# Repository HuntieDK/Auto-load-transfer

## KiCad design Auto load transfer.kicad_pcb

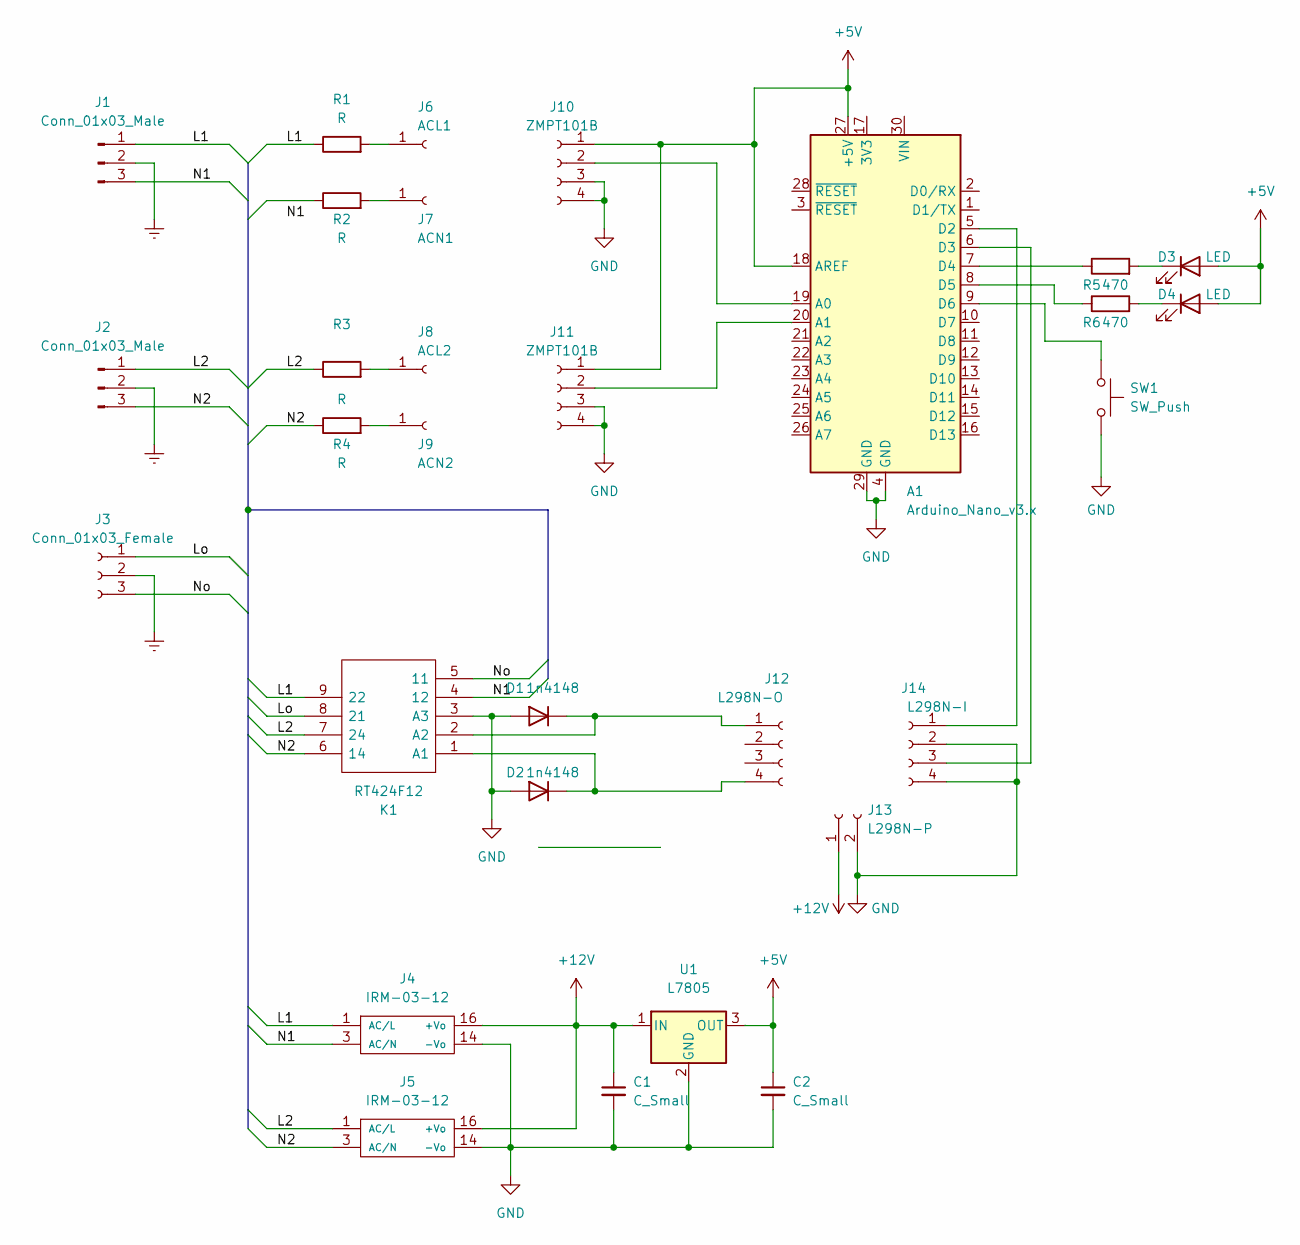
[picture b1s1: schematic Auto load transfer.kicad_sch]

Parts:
A1: Arduino_Nano_v3.x; Arduino_Nano
C1, C2: C_Small; C_Disc_D5.0mm_W2.5mm_P5.00mm
D1, D2: 1n4148; D_DO-35_SOD27_P7.62mm_Horizontal
D3, D4: LED; TerminalBlock_bornier-2_P5.08mm
J1, J2: Conn_01x03_Male; TerminalBlock_bornier-3_P5.08mm
J3: Conn_01x03_Female; TerminalBlock_bornier-3_P5.08mm
J4, J5: IRM-03-12; MeanWell_IRM
J6: ACL1; MountingHole_2.2mm_M2_DIN965_Pad
J7: ACN1; MountingHole_2.2mm_M2_DIN965_Pad
J8: ACL2; MountingHole_2.2mm_M2_DIN965_Pad
J9: ACN2; MountingHole_2.2mm_M2_DIN965_Pad
J10, J11: ZMPT101B; PinHeader_1x04_P2.54mm_Vertical
J12: L298N-O; PinHeader_1x04_P2.54mm_Vertical
J13: L298N-P; PinHeader_1x02_P2.54mm_Vertical
J14: L298N-I; PinHeader_1x04_P2.54mm_Vertical
K1: RT424F12; Manufacturer_Part_Number RT424F12; Mouser Part Number 655-RT424F12
R1, R2, R3, R4: R; R_Axial_DIN0309_L9.0mm_D3.2mm_P12.70mm_Horizontal
R5, R6: 470; R_Axial_DIN0309_L9.0mm_D3.2mm_P12.70mm_Horizontal
SW1: SW_Push; TerminalBlock_bornier-2_P5.08mm
U1: L7805; TO-220-3_Vertical

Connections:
+5V: A1.18 (AREF), A1.27 (+5V), C2.1, D3.2 (A), D4.2 (A), J10.1, J11.1, U1.3 (OUT)
+12V: C1.1, J4.16 (+Vo), J5.16 (+Vo), J13.1, U1.1 (IN)
/L1: J1.1, J4.1 (AC/L), K1.9 (22), R1.1
/L2: J2.1, J5.1 (AC/L), K1.7 (24), R3.1
/Lo: J3.1, K1.8 (21)
/N1: J1.3, J4.3 (AC/N), K1.4 (12)
/N2: J2.3, J5.3 (AC/N), K1.6 (14), R4.1
/No: J3.3, K1.5 (11)
Earth: J1.2, J2.2, J3.2
GND: A1.4 (GND), A1.29 (GND), C1.2, C2.2, D1.2 (A), D2.2 (A), J4.14 (-Vo), J5.14 (-Vo), J10.3, J10.4, J11.3, J11.4, J13.2, J14.2, J14.4, K1.3 (A3), SW1.2, U1.2 (GND)
unnamed: A1.5 (D2), J14.1
unnamed: A1.6 (D3), J14.3
unnamed: A1.7 (D4), R5.1
unnamed: A1.8 (D5), R6.1
unnamed: A1.9 (D6), SW1.1
unnamed: A1.19 (A0), J10.2
unnamed: A1.20 (A1), J11.2
unnamed: D2.1 (K), J12.4, K1.1 (A1)
unnamed: D3.1 (K), R5.2
unnamed: D4.1 (K), R6.2
unnamed: J6.1, R1.2
unnamed: J7.1, R2.2
unnamed: J8.1, R3.2
unnamed: J9.1, R4.2
unnamed: D1.1 (K), J12.1, K1.2 (A2)

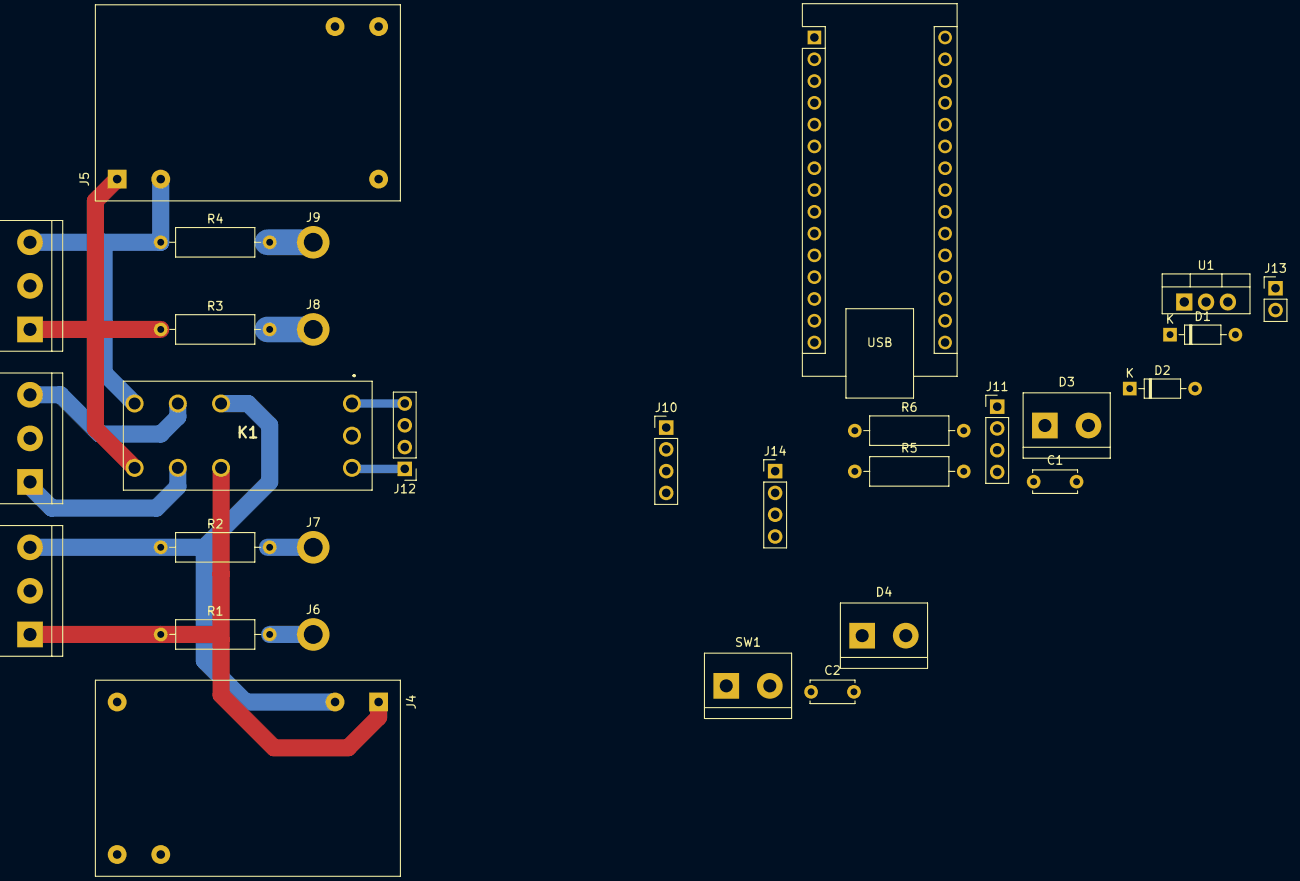
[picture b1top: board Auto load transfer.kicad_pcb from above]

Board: 2 copper layers, 30 parts (0 on the bottom side), 25 nets.

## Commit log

2023-08-30 Initial schematics
2023-08-30 Added some decoupling
2023-10-30 Change to Arduino based block diagram
2023-11-05 Prepare for PCB layout
2023-11-13 PCB layout beginning
